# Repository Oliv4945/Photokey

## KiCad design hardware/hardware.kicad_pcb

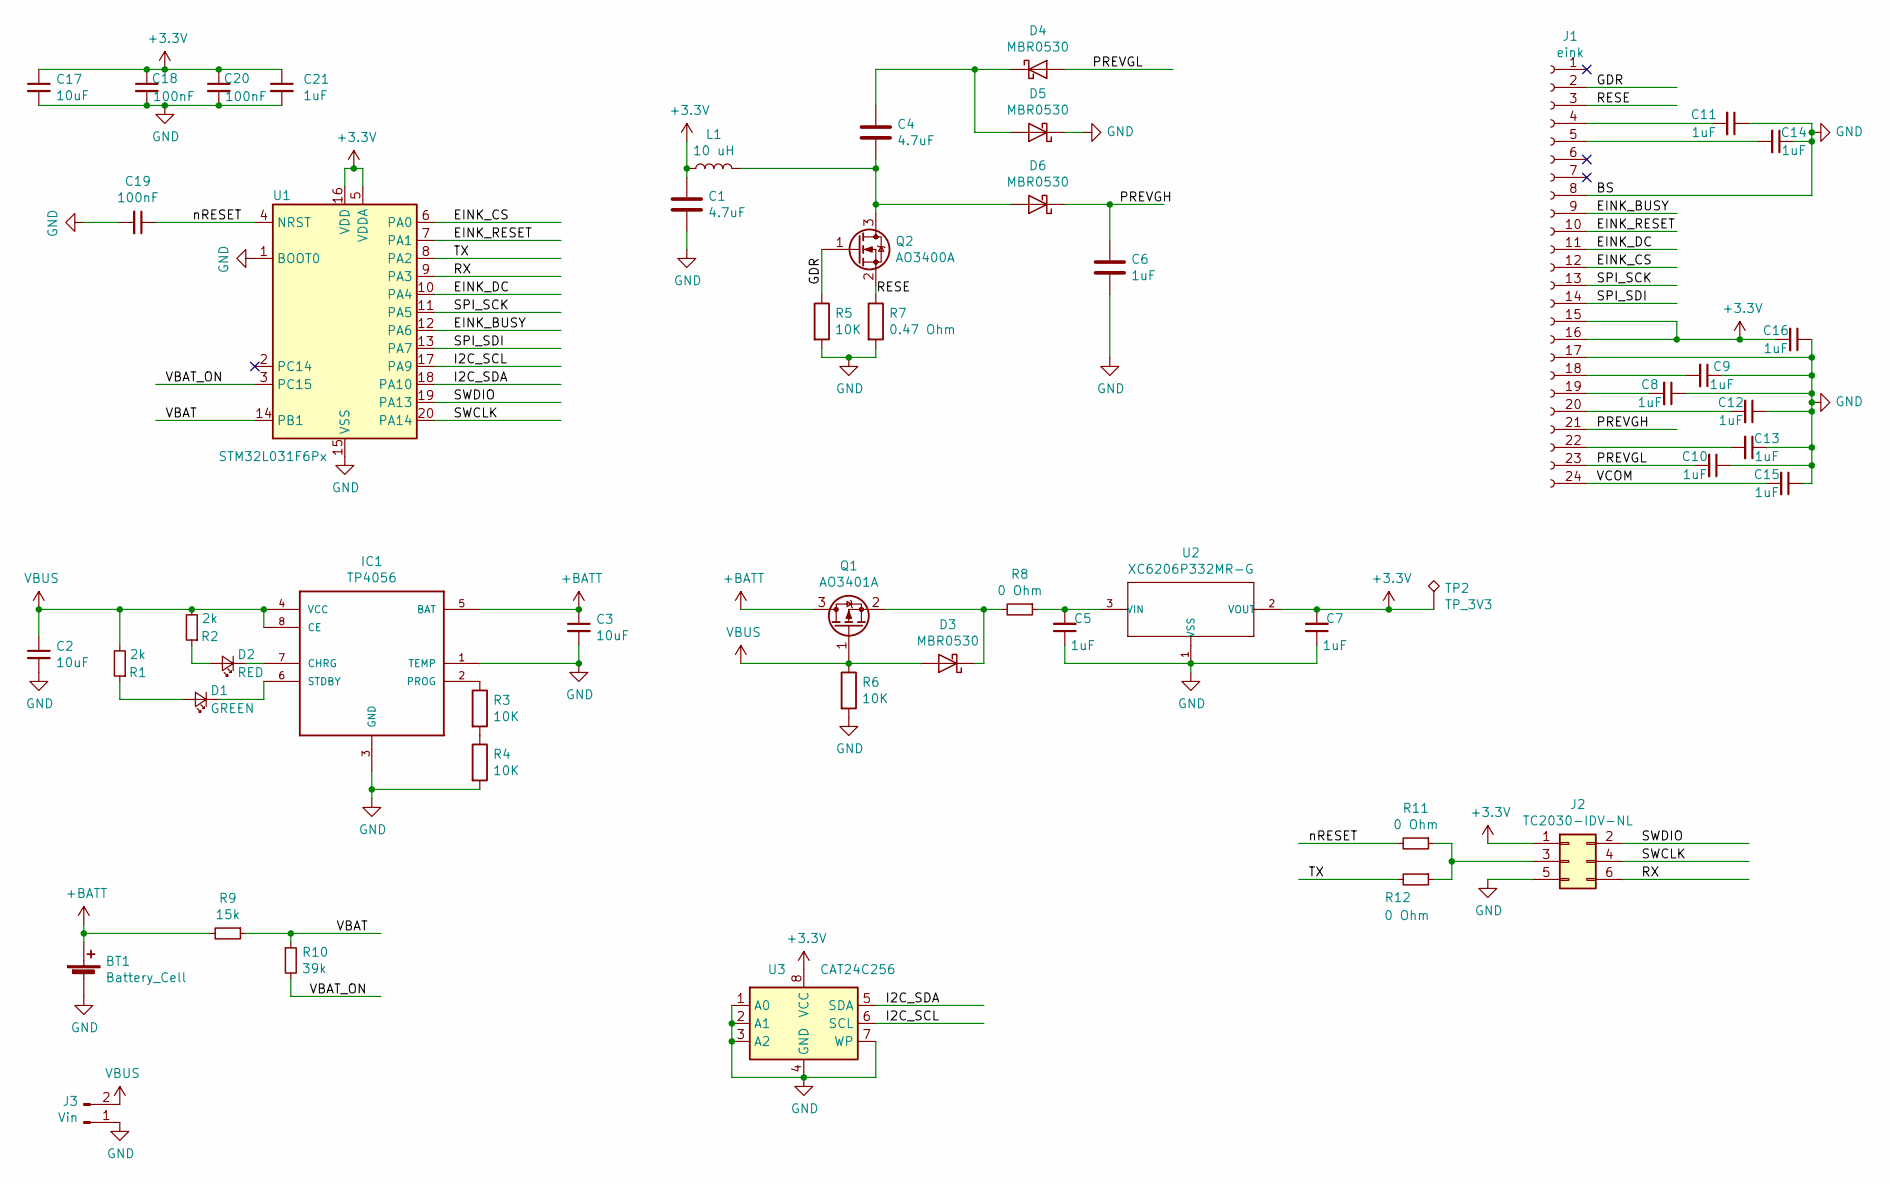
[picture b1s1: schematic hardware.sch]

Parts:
BT1: Battery_Cell; 2450
C1, C4: 4.7uF; C_1206_3216Metric; LCSC C29823
C2, C3, C17: 10uF; C_0805_2012Metric; LCSC C15850
C5, C6, C7, C8, C9, C10, C11, C12, C13, C14, C15, C16, C21: 1uF; C_0603_1608Metric; LCSC C15849
C18, C19, C20: 100nF; C_0402_1005Metric; LCSC C1525
D1: GREEN; D_0603_1608Metric; LCSC C72043
D2: RED; D_0603_1608Metric; LCSC C2286
D3, D4, D5, D6: MBR0530; D_SOD-123; LCSC C232832
IC1: TP4056; SOP-8; LCSC C16581
J1: eink; FPC_24
J2: TC2030-IDV-NL; TC2030-MCP-NL
J3: Vin; PinHeader_1x02_P2.54mm_Vertical
L1: 10 uH; L_1210_3225Metric; LCSC C86069
Q1: AO3401A; SOT-23; LCSC C15127
Q2: AO3400A; SOT-23; LCSC C20917
R1, R2: 2k; R_0402_1005Metric; LCSC C4109
R3, R4, R5, R6: 10K; R_0402_1005Metric; LCSC C25744
R7: 0.47 Ohm; R_0603_1608Metric; LCSC C23411
R8, R11, R12: 0 Ohm; R_0402_1005Metric; LCSC C21189
R9: 15k; R_0402_1005Metric; LCSC C25756
R10: 39k; R_0402_1005Metric; LCSC C25783
TP2: TP_3V3; TestPoint_Pad_D1.5mm
U1: STM32L031F6Px; TSSOP-20_4.4x6.5mm_P0.65mm; LCSC C115208
U2: XC6206P332MR-G; SOT-23; LCSC C5446
U3: CAT24C256; SOIC-8_3.9x4.9mm_P1.27mm; LCSC C6482

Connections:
+3V3: C1.1, C7.2, C16.2, C17.1, C18.1, C20.1, C21.1, J1.15, J1.16, J2.1, L1.1, TP2.1, U1.5 (VDDA), U1.16 (VDD), U2.2 (VOUT), U3.8 (VCC)
+BATT: BT1.1 (+), C3.1, IC1.5 (BAT), Q1.3 (D), R9.2
/EINK_BUSY: J1.9, U1.12 (PA6)
/EINK_CS: J1.12, U1.6 (PA0)
/EINK_DC: J1.11, U1.10 (PA4)
/EINK_RESET: J1.10, U1.7 (PA1)
/GDR: J1.2, Q2.1 (G), R5.1
/I2C_SCL: U1.17 (PA9), U3.6 (SCL)
/I2C_SDA: U1.18 (PA10), U3.5 (SDA)
/PREVGH: C6.1, D6.1 (K), J1.21
/PREVGL: C10.2, D4.2 (A), J1.23
/RESE: J1.3, Q2.2 (S), R7.1
/RX: J2.6, U1.9 (PA3)
/SPI_SCK: J1.13, U1.11 (PA5)
/SPI_SDI: J1.14, U1.13 (PA7)
/SWCLK: J2.4, U1.20 (PA14)
/SWDIO: J2.2, U1.19 (PA13)
/TX: R12.2, U1.8 (PA2)
/VBAT: R9.1, R10.1, U1.14 (PB1)
/VBAT_ON: R10.2, U1.3 (PC15)
/VCOM: C15.2, J1.24
/nRESET: C19.1, R11.2, U1.4 (NRST)
GND: BT1.2 (-), C1.2, C2.2, C3.2, C5.1, C6.2, C7.1, C8.1, C9.1, C10.1, C11.1, C12.1, C13.1, C14.1, C15.1, C16.1, C17.2, C18.2, C19.2, C20.2, C21.2, D5.1 (K), IC1.1 (TEMP), IC1.3 (GND), J1.8, J1.17, J2.5, J3.1, R4.2, R5.2, R6.2, R7.2, U1.1 (BOOT0), U1.15 (VSS), U2.1 (VSS), U3.1 (A0), U3.2 (A1), U3.3 (A2), U3.4 (GND), U3.7 (WP)
unnamed: C4.1, D4.1 (K), D5.2 (A)
unnamed: C4.2, D6.2 (A), L1.2, Q2.3 (D)
unnamed: C5.2, R8.1, U2.3 (VIN)
unnamed: C8.2, J1.19
unnamed: C9.2, J1.18
unnamed: C11.2, J1.4
unnamed: C12.2, J1.20
unnamed: C13.2, J1.22
unnamed: C14.2, J1.5
unnamed: D1.1 (K), IC1.6 (STDBY)
unnamed: D1.2 (A), R1.1
unnamed: D2.1 (K), IC1.7 (CHRG)
unnamed: D2.2 (A), R2.1
unnamed: D3.1 (K), Q1.2 (S), R8.2
unnamed: IC1.2 (PROG), R3.1
unnamed: J2.3, R11.1, R12.1
unnamed: R3.2, R4.1
VBUS: C2.1, D3.2 (A), IC1.4 (VCC), IC1.8 (CE), J3.2, Q1.1 (G), R1.2, R2.2, R6.1

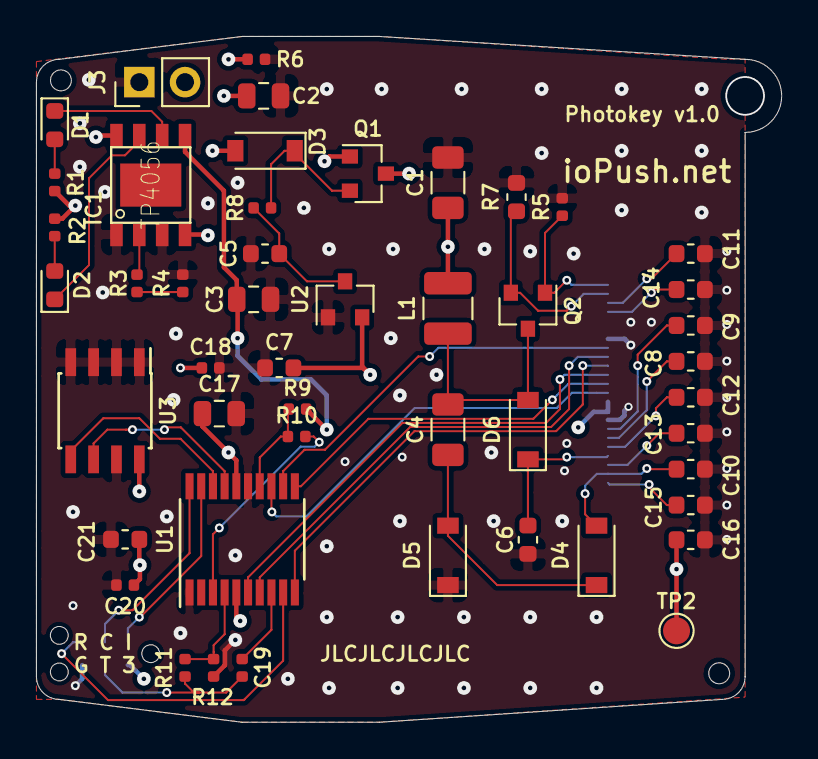
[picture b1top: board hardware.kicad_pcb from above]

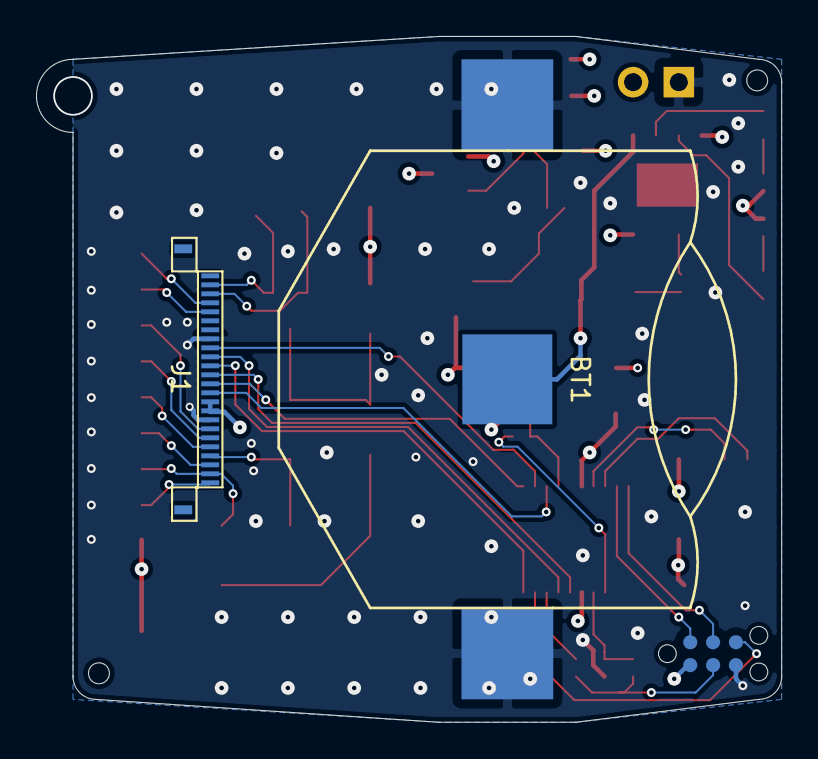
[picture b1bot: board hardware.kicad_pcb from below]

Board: 4 copper layers, 41.4 x 38.1 mm, 51 parts (3 on the bottom side), 41 nets.

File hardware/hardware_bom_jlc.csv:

"Comment","Designator","Footprint","LCSC Part #"
"4.7uF","C1,C4","C_1206_3216Metric","C29823"
"10uF","C2,C3,C17","C_0805_2012Metric","C15850"
"1uF","C6,C11,C14,C16,C9,C8,C12,C13,C10,C15,C5,C7,C21","C_0603_1608Metric","C15849"
"100nF","C19,C20,C18","C_0402_1005Metric","C1525"
"GREEN","D1","D_0603_1608Metric","C72043"
"RED","D2","D_0603_1608Metric","C2286"
"MBR0530","D4,D5,D6,D3","D_SOD-123","C232832"
"TP4056","IC1","SOP-8","C16581"
"10 uH","L1","L_1210_3225Metric","C86069"
"AO3401A","Q1","SOT-23","C15127"
"AO3400A","Q2","SOT-23","C20917"
"2k","R2,R1","R_0402_1005Metric","C4109"
"10K","R5,R4,R3,R6","R_0402_1005Metric","C25744"
" 0.47 Ohm","R7","R_0603_1608Metric","C23411"
"0 Ohm","R8,R11,R12","R_0402_1005Metric","C21189"
"15k","R9","R_0402_1005Metric","C25756"
"39k","R10","R_0402_1005Metric","C25783"
"STM32L031F6Px","U1","TSSOP-20_4.4x6.5mm_P0.65mm","C115208"
"XC6206P332MR-G","U2","SOT-23","C5446"
"CAT24C256","U3","SOIC-8_3.9x4.9mm_P1.27mm","C6482"

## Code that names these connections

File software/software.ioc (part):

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Mcu.Name=STM32L031F(4-6)Px
Mcu.Package=TSSOP20
Mcu.UserName=STM32L031F6Px
PA0-CK_IN.GPIOParameters=GPIO_Label
PA0-CK_IN.GPIO_Label=EINK_CS
PA0-CK_IN.Signal=GPIO_Output
PA1.GPIOParameters=GPIO_Label
PA1.GPIO_Label=EINK_RESET
PA1.Signal=GPIO_Output
PA10.GPIOParameters=GPIO_Label
PA10.GPIO_Label=I2C_SDA
PA10.Mode=I2C
PA10.Signal=I2C1_SDA
PA13.Mode=Serial_Wire
PA13.Signal=SYS_SWDIO
PA14.Mode=Serial_Wire
PA14.Signal=SYS_SWCLK
PA2.Mode=Asynchronous
PA2.Signal=LPUART1_TX
PA3.Mode=Asynchronous
PA3.Signal=LPUART1_RX
PA4.GPIOParameters=GPIO_Label
PA4.GPIO_Label=EINK_DC
PA4.Signal=GPIO_Output
PA5.GPIOParameters=GPIO_Label
PA5.GPIO_Label=SPI_SCK
PA5.Mode=TX_Only_Simplex_Unidirect_Master
PA5.Signal=SPI1_SCK
PA6.GPIOParameters=GPIO_Label
PA6.GPIO_Label=EINK_BUSY
PA6.Signal=GPIO_Input
PA7.GPIOParameters=GPIO_Label
PA7.GPIO_Label=SPI_SDI
PA7.Mode=TX_Only_Simplex_Unidirect_Master
PA7.Signal=SPI1_MOSI
PA9.GPIOParameters=GPIO_Label
PA9.GPIO_Label=I2C_SCL
PA9.Mode=I2C
PA9.Signal=I2C1_SCL
PB1.GPIOParameters=GPIO_Label
PB1.GPIO_Label=VBAT
PB1.Mode=IN9
PB1.Signal=ADC_IN9
PC15-OSC32_OUT.GPIOParameters=GPIO_Label,GPIO_ModeDefaultOutputPP
PC15-OSC32_OUT.GPIO_Label=VBAT_ON
PC15-OSC32_OUT.GPIO_ModeDefaultOutputPP=GPIO_MODE_OUTPUT_OD
PC15-OSC32_OUT.Signal=GPIO_Output
RCC.HSE_VALUE=8000000
RCC.SYSCLKFreq_VALUE=2097000
board=custom

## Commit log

2019-12-09 Schematic done
2019-12-09 Add J1 connector
2019-12-11 Placed components
2019-12-13 Update voltage divider
2019-12-13 Board routed
2019-12-13 Add production files
2020-01-02 Code init
2020-01-02 Add EEPROM
2020-01-03 WIP - 4 greyscale image converter
2020-01-22 init epd
2020-01-22 Code refactoring
2020-01-22 Fixed SPI to transmit only
2020-01-26 Update eink management code - working
2020-01-26 Working script for 4 bits colors
2020-02-02 Add 2 black/white eink
2020-02-05 Select same direction in screen than BMP
2020-02-05 Read color map from BMP header
2020-02-06 All image processing done on computer
2020-02-07 Remove useless SPI delays
2020-02-07 Add battery simulation from measurements
2020-02-10 Update battery calculator
2020-02-10 Basic low power
2020-02-10 Add RTC and update sleep
2020-02-14 Refactor Python filename handling
2020-02-14 Reformat with Black
2020-02-16 Make convert.py executable
2020-03-02 Switch I2C to fastplus
2020-03-02 Correct eeprom read size to 16 bits
2020-03-02 Load image from EEPROM
